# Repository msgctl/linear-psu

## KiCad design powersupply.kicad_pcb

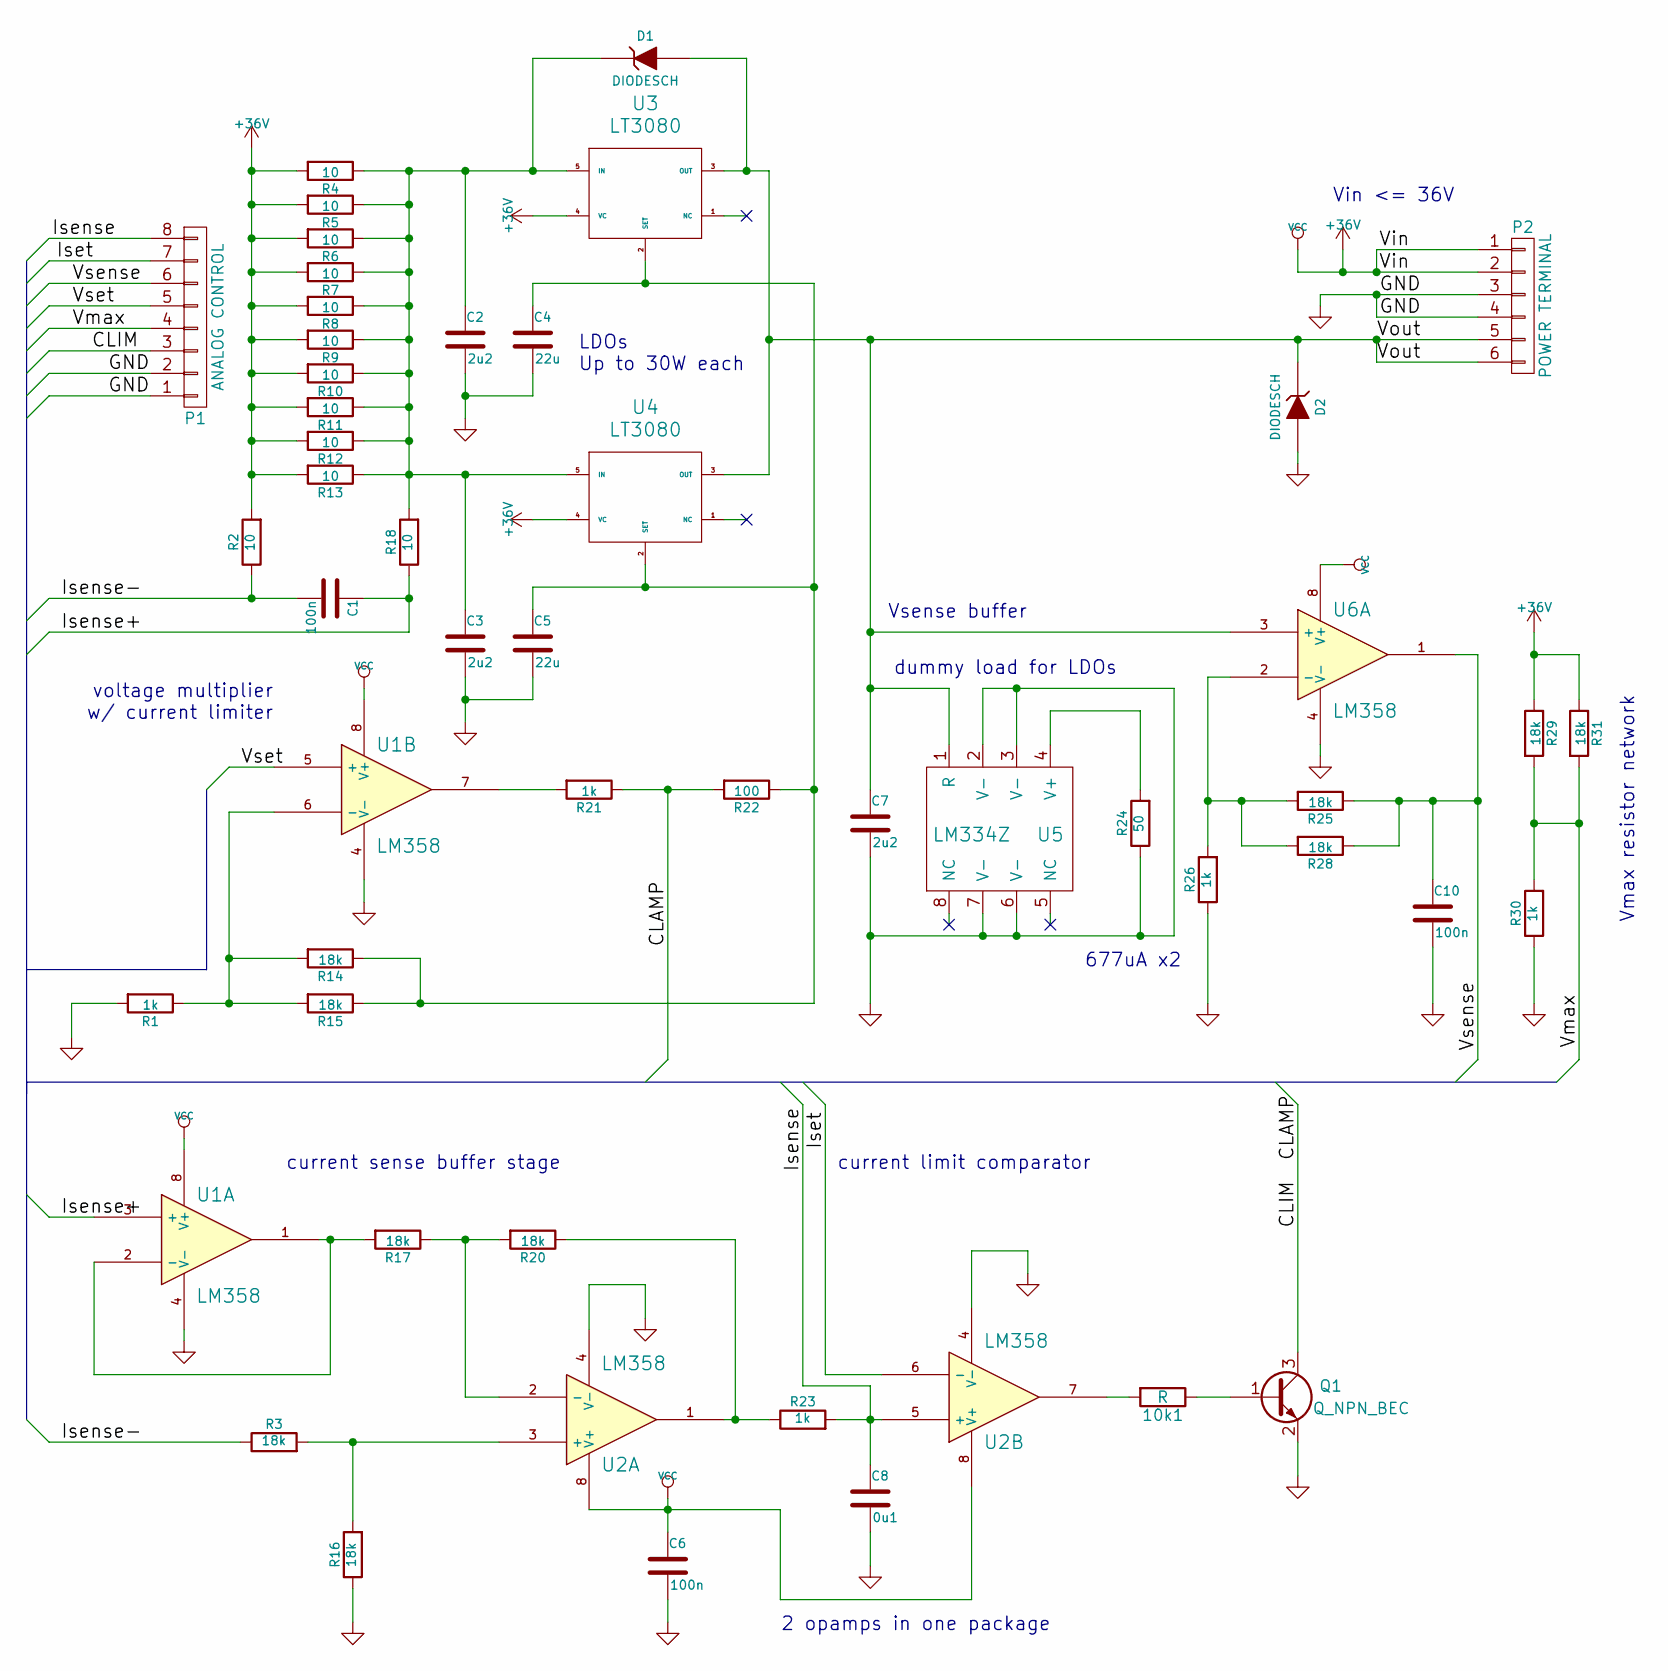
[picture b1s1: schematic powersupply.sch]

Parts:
10k1: R; R_0805
C1, C6, C10: 100n; 0805
C2, C3, C7: 2u2; 0805
C4, C5: 22u; 0805
C8: 0u1; 0805
D1, D2: DIODESCH; D-SOD123
P1: ANALOG CONTROL; Socket_Strip_Straight_1x08
P2: POWER TERMINAL; mstba_2,5%2f6-g-5,08
Q1: Q_NPN_BEC; SOT-23
R1, R21, R23, R26, R30: 1k; 0805R
R2, R18: 10; 0805R
R3, R14, R15, R16, R17, R20, R25, R28, R29, R31: 18k; 0805R
R4, R5, R6, R7, R8, R9, R10, R11, R12, R13: 10; 2512R
R22: 100; 0805R
R24: 50; 0805R
U1, U2, U6: LM358; SOIC8N
U3, U4: LT3080; Pentawatt_Neutral_Staggered_Verical_TO220-5-T05D
U5: LM334Z; SOIC8N

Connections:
+36V: C6.1, P2.1, P2.2, R2.2, R4.2, R5.2, R6.2, R7.2, R8.2, R9.2, R10.2, R11.2, R12.2, R13.2, R29.1, R31.1, U1.8 (V+), U2.8 (V+), U3.4 (VC), U4.4 (VC), U6.8 (V+)
/CLAMP: P1.3, Q1.3 (C), R21.1, R22.2
/Isense: C8.1, P1.8, R23.2, U2.5 (+)
/Isense+: C1.1, R18.1, U1.3 (+)
/Isense-: C1.2, R2.1, R3.1
/Iset: P1.7, U2.6 (-)
/Vmax: P1.4, R29.2, R30.2, R31.2
/Vout: C7.1, D1.2 (A), D2.1 (K), P2.5, P2.6, U3.3 (OUT), U4.3 (OUT), U5.1 (R), U6.3 (+)
/Vsense: C10.1, P1.6, R25.1, R28.1, U6.1
/Vset: P1.5, U1.5 (+)
GND: C2.2, C3.2, C4.2, C5.2, C6.2, C7.2, C8.2, C10.2, D2.2 (A), P1.1, P1.2, P2.3, P2.4, Q1.2 (E), R1.2, R16.1, R24.1, R26.1, R30.1, U1.4 (V-), U2.4 (V-), U5.2 (V-), U5.3 (V-), U5.6 (V-), U5.7 (V-), U6.4 (V-)
unnamed: 10k1.1, Q1.1 (B)
unnamed: 10k1.2, U2.7
unnamed: C2.1, C3.1, D1.1 (K), R4.1, R5.1, R6.1, R7.1, R8.1, R9.1, R10.1, R11.1, R12.1, R13.1, R18.2, U3.5 (IN), U4.5 (IN)
unnamed: C4.1, C5.1, R14.1, R15.1, R22.1, U3.2 (SET), U4.2 (SET)
unnamed: R1.1, R14.2, R15.2, U1.6 (-)
unnamed: R3.2, R16.2, U2.3 (+)
unnamed: R17.1, R20.2, U2.2 (-)
unnamed: R17.2, U1.1, U1.2 (-)
unnamed: R20.1, R23.1, U2.1
unnamed: R21.2, U1.7
unnamed: R24.2, U5.4 (V+)
unnamed: R25.2, R26.2, R28.2, U6.2 (-)

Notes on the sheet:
current sense buffer stage
current limit comparator
Vin <= 36V
dummy load for LDOs
Vsense buffer
LDOs Up to 30W each
677uA x2
voltage multiplier w/ current limiter
Vmax resistor network
2 opamps in one package

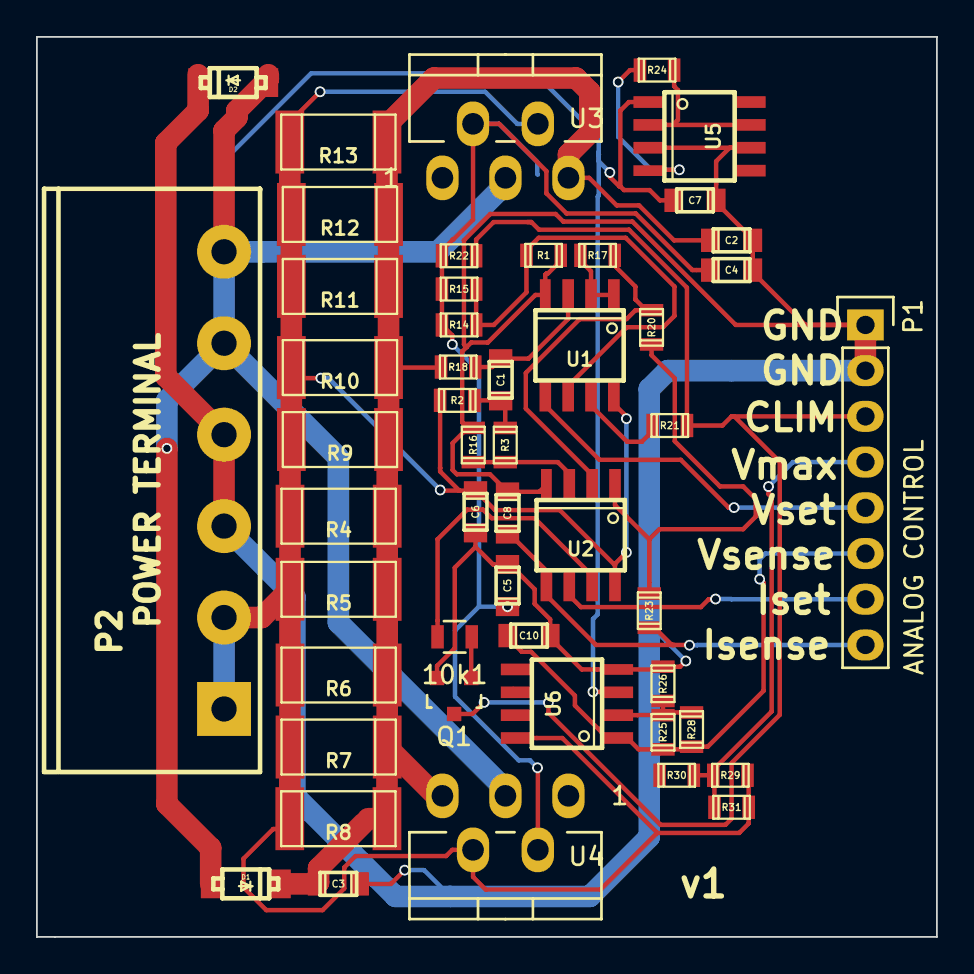
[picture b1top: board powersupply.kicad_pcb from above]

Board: 2 copper layers, 50.0 x 50.0 mm, 50 parts (0 on the bottom side), 23 nets.

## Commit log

2021-03-16 initial
